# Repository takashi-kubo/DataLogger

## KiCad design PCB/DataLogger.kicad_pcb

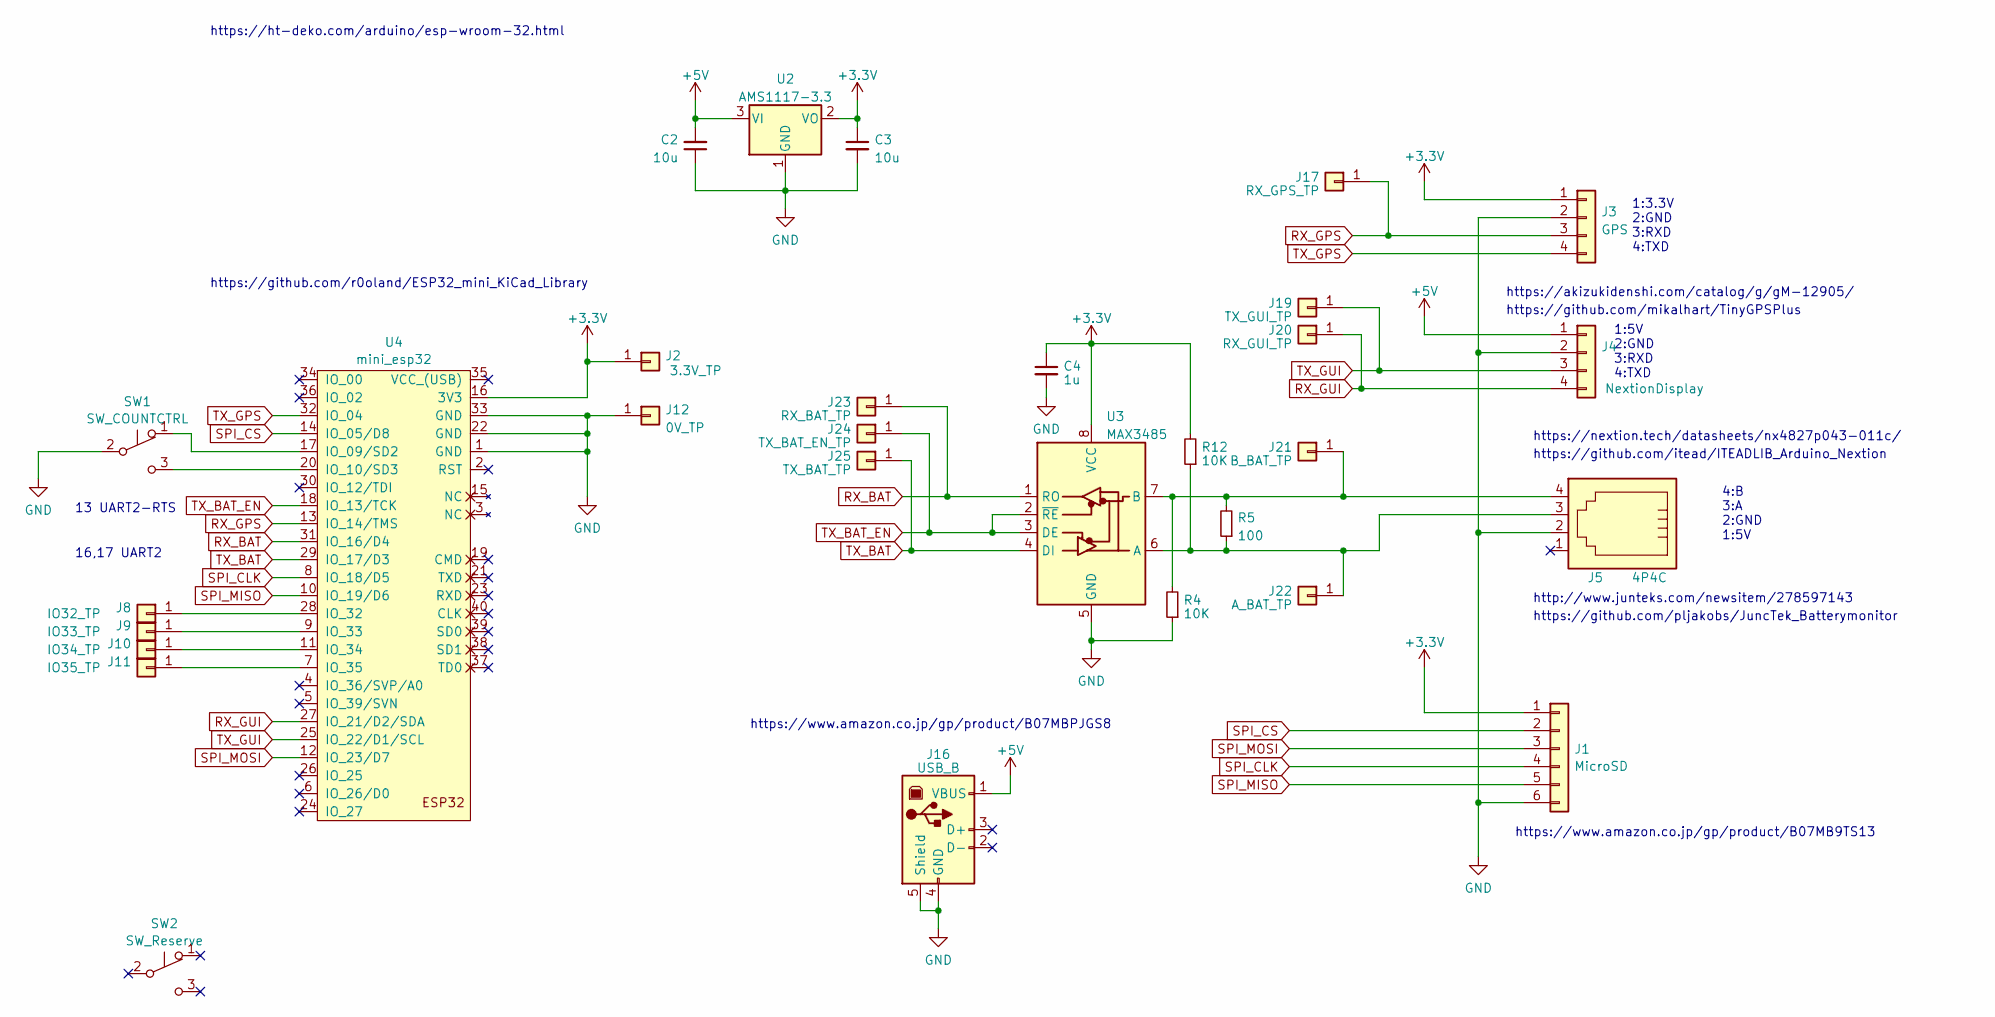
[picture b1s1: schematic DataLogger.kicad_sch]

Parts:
C2, C3: 10u; C_0603_1608Metric_Pad1.08x0.95mm_HandSolder
C4: 1u; C_0603_1608Metric_Pad1.08x0.95mm_HandSolder
J1: MicroSD; PinHeader_1x06_P2.54mm_Vertical
J2: 3.3V_TP; TestPoint_Pad_2.0x2.0mm
J3: GPS; JST_XH_B4B-XH-A_1x04_P2.50mm_Vertical
J4: NextionDisplay; JST_XH_B4B-XH-A_1x04_P2.50mm_Vertical
J5: 4P4C; 1-1705949-1
J8: IO32_TP; TestPoint_Pad_2.0x2.0mm
J9: IO33_TP; TestPoint_Pad_2.0x2.0mm
J10: IO34_TP; TestPoint_Pad_2.0x2.0mm
J11: IO35_TP; TestPoint_Pad_2.0x2.0mm
J12: 0V_TP; TestPoint_Pad_2.0x2.0mm
J16: USB_B; USB_B_TE_5787834_Vertical
J17: RX_GPS_TP; TestPoint_Pad_2.0x2.0mm
J19: TX_GUI_TP; TestPoint_Pad_2.0x2.0mm
J20: RX_GUI_TP; TestPoint_Pad_2.0x2.0mm
J21: B_BAT_TP; TestPoint_Pad_2.0x2.0mm
J22: A_BAT_TP; TestPoint_Pad_2.0x2.0mm
J23: RX_BAT_TP; TestPoint_Pad_2.0x2.0mm
J24: TX_BAT_EN_TP; TestPoint_Pad_2.0x2.0mm
J25: TX_BAT_TP; TestPoint_Pad_2.0x2.0mm
R4, R12: 10K; R_0603_1608Metric_Pad0.98x0.95mm_HandSolder
R5: 100; R_0603_1608Metric_Pad0.98x0.95mm_HandSolder
SW1: SW_COUNTCTRL; PinHeader_1x03_P2.54mm_Horizontal
SW2: SW_Reserve; PinHeader_1x03_P2.54mm_Horizontal
U2: AMS1117-3.3; SOT-223-3_TabPin2
U3: MAX3485; SOP-8_3.9x4.9mm_P1.27mm
U4: mini_esp32; ESP32_mini

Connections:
+3V3: C3.1, C4.1, J1.1, J2.1, J3.1, R12.2, U2.2 (VO), U3.8 (VCC), U4.16 (3V3)
+5V: C2.2, J4.1, J16.1 (VBUS), U2.3 (VI)
GND: C2.1, C3.2, C4.2, J1.6, J3.2, J4.2, J5.2, J12.1, J16.4 (GND), J16.5 (Shield), R4.1, SW1.2 (B), U2.1 (GND), U3.5 (GND), U4.1 (GND), U4.22 (GND), U4.33 (GND)
unnamed: J8.1, U4.28 (IO_32)
unnamed: J9.1, U4.9 (IO_33)
unnamed: J10.1, U4.11 (IO_34)
unnamed: J11.1, U4.7 (IO_35)
unnamed: J5.4, J21.1, R4.2, R5.2, U3.7 (B)
unnamed: J5.3, J22.1, R5.1, R12.1, U3.6 (A)
unnamed: SW1.1 (A), U4.17 (IO_09/SD2)
unnamed: SW1.3 (C), U4.20 (IO_10/SD3)
RX_BAT: J23.1, U3.1 (RO), U4.31 (IO_16/D4)
RX_GPS: J3.3, J17.1, U4.13 (IO_14/TMS)
RX_GUI: J4.4, J20.1, U4.27 (IO_21/D2/SDA)
SPI_CLK: J1.4, U4.8 (IO_18/D5)
SPI_CS: J1.2, U4.14 (IO_05/D8)
SPI_MISO: J1.5, U4.10 (IO_19/D6)
SPI_MOSI: J1.3, U4.12 (IO_23/D7)
TX_BAT: J25.1, U3.4 (DI), U4.29 (IO_17/D3)
TX_BAT_EN: J24.1, U3.2 (~RE), U3.3 (DE), U4.18 (IO_13/TCK)
TX_GPS: J3.4, U4.32 (IO_04)
TX_GUI: J4.3, J19.1, U4.25 (IO_22/D1/SCL)

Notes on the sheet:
https://www.amazon.co.jp/gp/product/B07MBPJGS8
https://github.com/pljakobs/JuncTek_Batterymonitor
1:3.3V 2:GND 3:RXD 4:TXD
https://www.amazon.co.jp/gp/product/B07MB9TS13
https://github.com/r0oland/ESP32_mini_KiCad_Library
http://www.junteks.com/newsitem/278597143
16,17 UART2
https://nextion.tech/datasheets/nx4827p043-011c/
https://github.com/itead/ITEADLIB_Arduino_Nextion
https://akizukidenshi.com/catalog/g/gM-12905/
https://ht-deko.com/arduino/esp-wroom-32.html
4:B 3:A 2:GND 1:5V
https://github.com/mikalhart/TinyGPSPlus
1:5V 2:GND 3:RXD 4:TXD
13 UART2-RTS

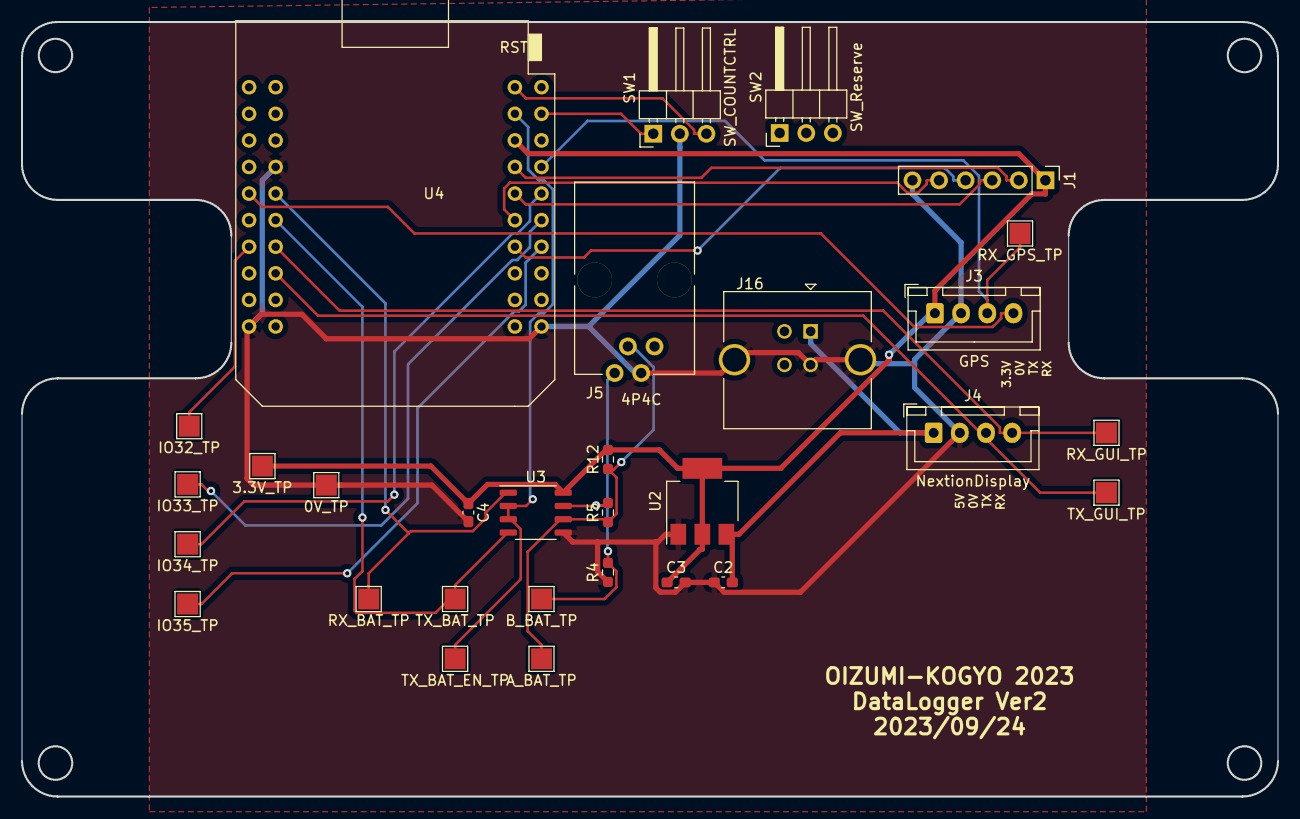
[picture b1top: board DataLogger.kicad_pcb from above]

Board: 2 copper layers, 120.0 x 74.0 mm, 30 parts (0 on the bottom side), 22 nets.

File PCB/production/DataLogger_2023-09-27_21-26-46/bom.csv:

Designator,Footprint,Quantity,Value,LCSC Part #
"C2, C3",0603,2,10u,
C4,0603,1,1u,
J1,PinHeader_1x06_P2.54mm_Vertical,1,MicroSD,
J10,TestPoint_Pad_2.0x2.0mm,1,IO34_TP,
J11,TestPoint_Pad_2.0x2.0mm,1,IO35_TP,
J12,TestPoint_Pad_2.0x2.0mm,1,0V_TP,
J16,USB_B_TE_5787834_Vertical,1,USB_B,
J17,TestPoint_Pad_2.0x2.0mm,1,RX_GPS_TP,
J19,TestPoint_Pad_2.0x2.0mm,1,TX_GUI_TP,
J2,TestPoint_Pad_2.0x2.0mm,1,3.3V_TP,
J20,TestPoint_Pad_2.0x2.0mm,1,RX_GUI_TP,
J21,TestPoint_Pad_2.0x2.0mm,1,B_BAT_TP,
J22,TestPoint_Pad_2.0x2.0mm,1,A_BAT_TP,
J23,TestPoint_Pad_2.0x2.0mm,1,RX_BAT_TP,
J24,TestPoint_Pad_2.0x2.0mm,1,TX_BAT_EN_TP,
J25,TestPoint_Pad_2.0x2.0mm,1,TX_BAT_TP,
J3,JST_XH_B4B-XH-A_1x04_P2.50mm_Vertical,1,GPS,
J4,JST_XH_B4B-XH-A_1x04_P2.50mm_Vertical,1,NextionDisplay,
J5,1-1705949-1,1,4P4C,
J8,TestPoint_Pad_2.0x2.0mm,1,IO32_TP,
J9,TestPoint_Pad_2.0x2.0mm,1,IO33_TP,
"R12, R4",0603,2,10K,
R5,0603,1,100,
SW1,PinHeader_1x03_P2.54mm_Horizontal,1,SW_COUNTCTRL,
SW2,PinHeader_1x03_P2.54mm_Horizontal,1,SW_Reserve,
U2,SOT-223-3_TabPin2,1,AMS1117-3.3,
U3,SOP-8_3.9x4.9mm_P1.27mm,1,MAX3485,
U4,ESP32_mini,1,mini_esp32,

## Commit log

2023-06-01 KG-F,GPS,ConnectionOK
2023-06-01 connectionOK
2023-06-29 no comment
2023-07-14 initial
2023-07-14 Add dependency library
2023-07-15 modify dependency library
2023-07-15 Modify Display Baud Rate For Noise Reduction
2023-09-29 devide testcode
2023-10-08 ADD NiMH discharge curve
2023-10-09 improvement bm monitoring and battery capacity display digit
2023-10-23 add pcb data
2023-10-23 Create LICENSE
2023-10-23 ADD display information
2023-10-26 PCB Data moved to new repository. new repository is Datalogger_PCB
2023-10-26 PCB data moved to new repository
2023-10-31 improved display refresh and smoozing data.
2025-12-10 works but need clean

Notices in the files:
parts and their libraries:
Copyright 2021 Accelerated Designs. All rights reserved.
